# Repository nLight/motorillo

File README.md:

# Motorillo 🎬

> **Precision stepper motor controller with WebUSB interface for camera sliders, timelapses, and automation projects.**

## ✨ Features

- 🌐 **Browser Control**: Direct WebUSB communication - no drivers needed
- 📱 **Dual Interface**: Standalone OLED menu + web interface
- 💾 **Persistent Storage**: Save up to 5 programs in EEPROM
- ⚡ **Precision Control**: Customizable speed (1ms to 4.3M ms per step)
- 🔄 **Auto-Recovery**: Graceful USB disconnection handling
- 🎯 **Infinite Programs**: Forward/backward motion until manually stopped
- 📊 **Real-time Feedback**: Live position and status updates

## 🚀 Quick Start

### Hardware Requirements

| Component          | Specification                               |
| ------------------ | ------------------------------------------- |
| **Arduino Board**  | Leonardo/Micro/Zero (WebUSB compatible)     |
| **Stepper Motor**  | 200 steps/revolution with compatible driver |
| **Driver**         | A4988, TMC2209                              |
| **Display**        | SSD1306 OLED 96×16 pixels (I2C)             |
| **Control Button** | Momentary push button                       |

### Connections

```
Arduino Leonardo/Micro:
├── Pin 10 → Stepper DIR
├── Pin 16 → Stepper STEP
├── Pin 2  → Control Button (internal pullup)
├── SDA/SCL → OLED Display (I2C)
└── USB → Computer (WebUSB + Power)
```

### Installation

1. **Clone the repository:**

   ```bash
   git clone https://github.com/yourusername/motorillo.git
   cd motorillo
   ```

2. **Upload firmware:**

   - Open `steppper.ino` in Arduino IDE
   - Install required libraries (see [Setup Guide](docs/setup/installation.md))
   - Upload to your Arduino board

3. **Access web interface:**
   - Serve the `webusb/` folder on localhost
   - Connect via Chrome/Edge browser
   - Click "Connect Slider" to establish WebUSB connection

## 📖 Documentation

- 📋 **[Setup Guide](docs/setup/)** - Hardware assembly and software installation
- 🛠 **[User Manual](docs/features/)** - Operating modes and program creation
- 👨‍💻 **[Development](docs/development/)** - Architecture and API reference
- 🔧 **[Troubleshooting](docs/setup/troubleshooting.md)** - Common issues and solutions

## 💡 Use Cases

- **📹 Camera Sliders**: Smooth motion for video production
- **⏱ Timelapse Photography**: Ultra-slow motion over hours/days
- **🏭 Automation**: Precise positioning for manufacturing
- **🎓 Education**: Learn motor control and WebUSB programming
- **🔬 Research**: Laboratory positioning systems

## 🎮 Control Modes

### Standalone Mode (OLED + Button)

- Navigate stored programs with push button
- View current position and status
- Start/stop/pause program execution

### WebUSB Mode (Browser Interface)

- Create and save motion programs
- Manual jog controls with custom speed
- Real-time monitoring and control
- Bulk program management

## 🔧 Technical Specifications

| Parameter          | Range                           | Default    |
| ------------------ | ------------------------------- | ---------- |
| **Speed Range**    | 1ms - 4,294,967,295ms per step  | 1000ms     |
| **Max Programs**   | 5 stored programs               | -          |
| **Position Range** | 0 - 65,535 steps                | 2000 steps |
| **Loop Programs**  | Infinite until manually stopped | -          |
| **Memory Usage**   | ~1KB EEPROM                     | -          |

## 🏗 Architecture

```
┌─────────────────┐    ┌──────────────────┐
│   Web Browser   │◄──►│   Pro Micro      │
│   (WebUSB UI)   │    │   (Motorillo)    │
└─────────────────┘    └──────────────────┘
                                │
                        ┌───────┴───────┐
                        │ Stepper Motor │
                        │   + Driver    │
                        └───────────────┘
```

**Modular Firmware:**

- `motor_control` - Movement and positioning
- `command_processor` - WebUSB communication
- `config_manager` - EEPROM storage
- `display_manager` - OLED interface
- `menu_system` - Standalone navigation

## 🤝 Contributing

We welcome contributions! Please see our [Development Guide](docs/development/) for:

- Code architecture overview
- Building and testing procedures
- Pull request guidelines

## 📚 Complete Documentation

This README provides a quick overview. For comprehensive documentation:

- **[Setup & Installation](docs/setup/)** - Hardware wiring, software installation, troubleshooting
- **[Features & Usage](docs/features/)** - User manual, speed control, WebUSB features
- **[Development](docs/development/)** - Architecture, API reference, protocol details

Start with the [Documentation Index](docs/README.md) for easy navigation.

## 📄 License

This project is licensed under the MIT License - see the [LICENSE](LICENSE) file for details.

## 🙏 Acknowledgments

- Built with Arduino framework and WebUSB standard
- OLED support via Adafruit libraries
- Inspired by the maker community's creativity

---

**Ready to automate your motion?** [Get started with the setup guide](docs/setup/) →

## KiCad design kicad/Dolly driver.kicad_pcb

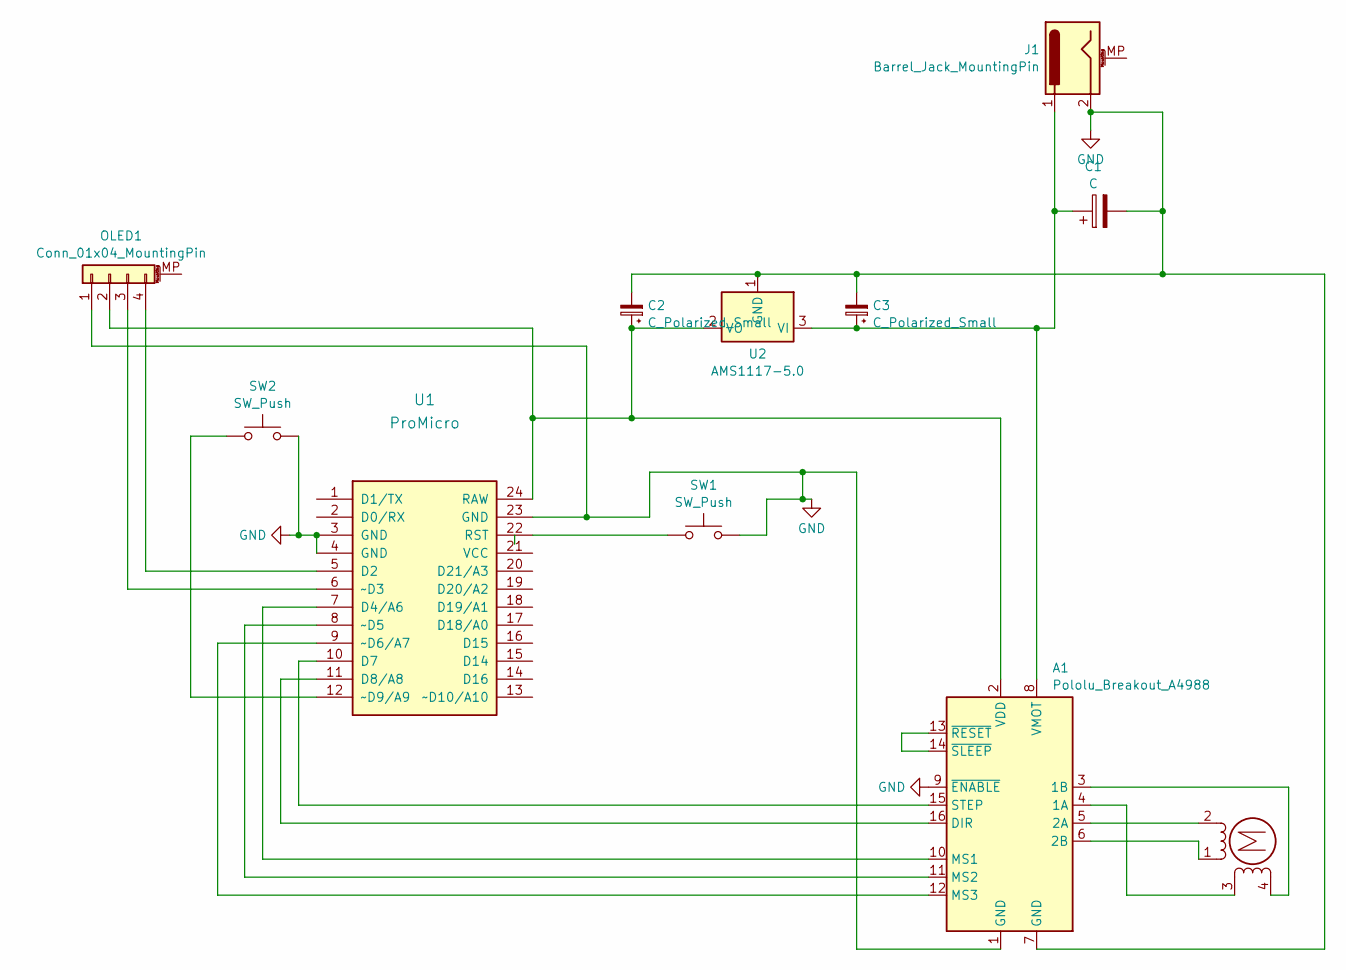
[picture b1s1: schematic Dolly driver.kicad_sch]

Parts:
A1: Pololu_Breakout_A4988; Pololu_Breakout-16_15.2x20.3mm
C1: C; CP_Radial_D6.3mm_P2.50mm
C2, C3: C_Polarized_Small; CP_Radial_D5.0mm_P2.50mm
J1: Barrel_Jack_MountingPin; BarrelJack_GCT_DCJ200-10-A_Horizontal
M1: Stepper_Motor_bipolar; PinHeader_1x04_P2.54mm_Vertical
OLED1: Conn_01x04_MountingPin; PinHeader_1x04_P2.54mm_Vertical
SW1, SW2: SW_Push; SW_Tactile_SPST_NO_Straight_CK_PTS636Sx25SMTRLFS
U1: ProMicro; ArduinoProMicro
U2: AMS1117-5.0; SOT-223-3_TabPin2

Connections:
GND: A1.1 (GND), A1.7 (GND), A1.9 (~ENABLE), C1.2, C2.2, C3.2, J1.2, OLED1.1 (GND), SW1.2, SW2.2, U1.3 (GND), U1.4 (GND), U1.23 (GND), U2.1 (GND)
unnamed: A1.4 (1A), M1.3
unnamed: A1.3 (1B), M1.4
unnamed: A1.5 (2A), M1.2 (-)
unnamed: A1.6 (2B), M1.1
unnamed: A1.16 (DIR), U1.11 (D8/A8)
unnamed: A1.10 (MS1), U1.7 (D4/A6)
unnamed: A1.11 (MS2), U1.8 (~D5)
unnamed: A1.12 (MS3), U1.9 (~D6/A7)
unnamed: A1.15 (STEP), U1.10 (D7)
unnamed: A1.2 (VDD), C2.1, OLED1.2 (VCC), U1.24 (RAW), U2.2 (VO)
unnamed: A1.8 (VMOT), C1.1, C3.1, J1.1, U2.3 (VI)
unnamed: A1.13 (~RESET), A1.14 (~SLEEP)
unnamed: OLED1.3 (SCL), U1.6 (~D3)
unnamed: OLED1.4 (SDA), U1.5 (D2)
unnamed: SW1.1, U1.22 (RST)
unnamed: SW2.1, U1.12 (~D9/A9)

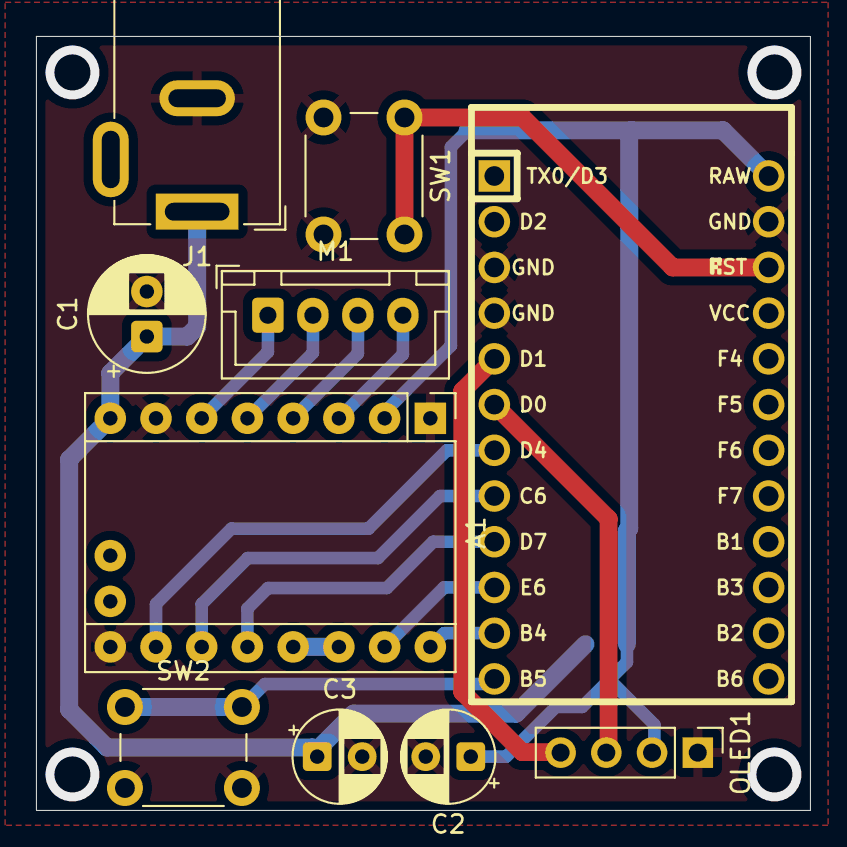
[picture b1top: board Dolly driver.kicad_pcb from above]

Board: 2 copper layers, 43.0 x 43.0 mm, 11 parts (1 on the bottom side), 17 nets.

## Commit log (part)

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2025-08-27 Init slider controller
2025-08-27 add menu
2025-08-27 optimize paued notification display
2025-08-27 Smooth menu behaviour
2025-08-27 improve display layout
2025-08-27 use both lines in prog
2025-08-27 Optimize programs
2025-08-27 optimize loops
2025-08-27 Bring back the animation
2025-09-05 Add motor control functionality and UI enhancements
    - Implement motor control logic in motor_control.cpp and motor_control.h.
    - Refactor main sketch (steppper.ino) to utilize modular motor control functions.
    - Update web interface to support speed unit selection (microseconds/milliseconds) for default speed and step speeds.
    - Enhance UI with new buttons for setting home position and improved layout for speed inputs.
    - Style adjustments in CSS for better user experience with speed input groups and home control buttons.
2025-09-05 Refactor program storage and management in config_manager
    - Introduced new program types: loop and complex, with efficient storage.
    - Added functions to save and load loop programs, including parameters for steps, delay, cycles, and speed unit.
    - Updated existing complex program functions to align with new storage format.
    - Enhanced EEPROM structure to accommodate new program types and sizes.
    - Implemented legacy functions for backward compatibility with existing complex programs.
    - Simplified motor control logic for running loop programs and handling movement.
2025-09-05 Enhance command processing and logging for loop programs
2025-09-05 Refactor configuration and motor control for improved clarity and efficiency
    - Updated SliderConfig structure to unify speed representation in milliseconds.
    - Reduced maximum program count from 10 to 5 to fit within EEPROM constraints.
    - Simplified speed conversion logic by removing speed unit handling.
    - Refactored motor control functions to use milliseconds directly for speed.
    - Enhanced loop and complex program handling with binary data transmission.
    - Updated web interface to reflect changes in speed input and program management.
2025-09-06 refactor(command): modularize command processing and simplify config handling
    - Removed configuration commands and related config management functionality
    - Added new bulk EEPROM loading command for efficient program data transfer
    - Simplified program management by embedding speed settings inside programs
    - Refactored command processing to handle binary commands centrally with command codes
    - Reduced EEPROM footprint by limiting max programs and storing
2025-09-06 refactor(config): remove complex program support, keep only loop programs
    - Simplify Config Manager to handle only loop program storage in EEPROM
    - Remove Complex program data structures and related functions from config_manager
    - Update program type enum to support only loop program type
    - Adjust processCommandCode to handle only loop programs, print error otherwise
    - Modify bulk EEPROM data handling to send and receive only loop programs
    - Remove legacy save/load complex program code from motor control and config_manager
2025-09-06 refactor(config): remove trailing blank lines and align comments
    - Removed unnecessary trailing blank lines in multiple source files
    - Adjusted inline comment spacing for better readability and consistency
    - Cleaned up extra blank lines in function definitions and code blocks
    - Improved code formatting without changing functionality
2025-09-06 fix(command_processor): remove redundant displayMessage call in processCommandCode
    - Deleted unnecessary displayMessage invocation before switch statement
    - Improved code clarity and efficiency in command processing function
2025-09-06 refactor(display): update display with dynamic position parameter
    - Modify updateDisplay function to accept a position argument with default currentPosition
    - Print position parameter on display instead of fixed currentPosition variable
    - Add newline characters after status text (PAUSE, RUN, STOP) for clearer formatting
    - Call updated display function during motor movement to show current step position in real time
2025-09-06 feat(display): enhance programming mode graphics and update status texts
    - Add drawing of shapes and lines for programming mode display
    - Change status texts from uppercase to capitalized format
    - Replace "PAUSE" with "Paused"
    - Replace "RUN" with "Running"
    - Replace "STOP" with "Stop"
    - Change "POS:" label to "Pos:" for position display
2025-09-06 feat(webusb): add manual movement velocity control with disconnection detection
    - Introduce velocity input control in WebUI for manual movement speed adjustment
    - Implement CMD_POS_WITH_SPEED and CMD_HOME_WITH_SPEED commands supporting custom speeds
    - Add input validation and persistence for manual speed using localStorage
    - Enhance Arduino firmware to handle new commands and move with specified speeds
    - Implement WebUSB disconnection detection with Arduino timeout and JavaScript event handling
    - Add periodic connection health check via CMD_DEBUG_INFO ping command
2025-09-06 refactor(commands): remove legacy commands
2025-09-06 fix(webusb): remove deprecated program options from dropdown
    - Removed Program 6 to Program 10 options from program selection dropdown
    - Simplified available program choices to first five options only
    - Cleaned up unused HTML option elements to improve clarity
2025-09-06 feat(display): add overloaded displayMessage function for regular strings
    - Implement displayMessage overload accepting String type messages
    - Clear display and set cursor before printing String message
    - Include optional duration delay and display update
    - Update header with new function declaration for String messages
2025-09-06 refactor(eeprom): send EEPROM data automatically on connection
    - Removed manual EEPROM data request handling in command processor
    - Added function to send all EEPROM loop programs immediately after WebUSB connection
    - Changed EEPROM data format to text lines with program count and individual program details
    - Updated WebUSB script to parse incoming text data for program count and programs
    - Eliminated redundant EEPROM data requests from web client
    - Improved UI updates and storage of loaded program data on web client side
2025-09-06 refactor(command): remove unused EEPROM data load command and related UI elements
    - Removed CMD_GET_ALL_DATA command from command_processor enum and logic
    - Deleted associated serial debug prints and processing code paths
    - Removed processCommand function and related calls to simplify command handling
    - Deleted "Load All from EEPROM" and "Clear Steps" buttons from web UI
    - Removed event listener and command code for requesting EEPROM data from webusb script
    - Cleaned up serial debug prints related to program execution and saving steps
2025-09-06 refactor(webusb): restructure directory and update resource paths
    - Move index.html from webusb/ to project root directory
    - Relocate script.js, serial.js, and styles.css into ui/ folder
    - Update stylesheet link in index.html to point to ./ui/styles.css
    - Update script sources in index.html to ./ui/serial.js and ./ui/script.js respectively
2025-09-06 docs(ui): update title and header to Motorillo - Camera Slider
    - Change page title from "Slider Controller - WebUSB" to "Motorillo - Camera Slider"
    - Update main header text from "Motorized Slider Controller" to "Motorillo - Camera Slider"
2025-09-06 refactor(loop): remove cycle count for loop programs and enable infinite running
    - Updated loop programs to run indefinitely until manually stopped
    - Removed cycles field from program data structures and UI
    - Simplified binary format by omitting cycles byte in loop program representation
    - Adjusted command processing and EEPROM storage to reflect infinite loops
    - Updated user interface tooltips and warnings to explain infinite loop behavior
    - Modified motor control logic to handle endless forward/backward motion with pause/stop checks
2025-09-06 fix(motor_control): call checkButton during motor movement and remove redundant delay code
    - Added checkButton() call inside moveToPositionWithSpeed to poll button state during movement
    - Removed obsolete cycling program delay logic in executeStoredProgram to simplify code flow
    - Retained error handling and idle delay behavior unchanged
2025-09-06 style(menu): reformat code for better readability and consistent indentation
    - Condensed single-line function definition for setupButton
    - Broke long if-condition into multiple lines in checkButton
    - Wrapped long function call arguments to multiple lines in buildMenuItems
    - Adjusted case statement indentations and spacing in selectMenuItem
    - Reordered statements in selectPauseMenuItem for logical flow
    - Ensured consistent usage of braces and spacing across functions
2025-09-06 fix(command): improve move command feedback and run status
    - Change display output to print move command with position and speed details
    - Set programRunning flag to true when move command is processed
    - Remove check for negative position in UI script input validation to allow zero or positive values
    - Clean up config_manager.h by removing obsolete default motor settings and comments
    - Adjust LoopProgram struct to indicate infinite running until stopped without cycles count
2025-09-06 refactor(motor_control): replace blocking delays with yieldingDelay function
    - Introduce yieldingDelay to split long delays into chunks and allow task responsiveness
    - Replace delay calls in moveToPositionWithSpeed with yieldingDelay for better multitasking
    - Use yieldingDelay in runLoopProgram and executeStoredProgram to improve responsiveness while paused or idling
    - Reduce updateDisplay frequency during motor movement to reduce overhead
    - Add yieldingDelay declaration to motor_control.h header for interface consistency
2025-09-06 refactor(motor_control): replace fixed yield with callback-based yielding delay
    - Introduce YieldCallback function pointer type for flexible yield handling
    - Add setYieldCallback() to register yield callback functions dynamically
    - Modify yieldingDelay() to invoke registered callback during delays
    - Replace direct checkButton() calls with yield callback invocation
    - Update motor control header to declare new callback functions
    - Set checkButton() as yield callback in setup for modular design
2025-09-11 fix(kicad): correct net numbering and update pad connections in Dolly driver PCB
    - Renumber nets for consistency and correct sequencing
    - Update pad net assignments to reflect new net numbers
    - Adjust thermal bridge width and gap for enable pad
    - Remove redundant pinfunction and pintype entries
    - Ensure GND and VMOT net references are aligned correctly
    - Correct pinfunction and pintype assignments for clarity
2025-09-12 fix(config): update default microstepping and display menu behaviour
    - Change default microstepping value from 1 to 8 due to motor settings update
    - Modify display menu to show "Programs:" label instead of current selection arrow
    - Adjust program listing format by printing index, total count, and program name on same line
    - Replace exitMenuMode call with enterMenuMode after showing current position and delay
    - Update motor control display refresh to divide step count by new default microstepping value to reduce overhead

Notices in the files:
README.md:
License: MIT
